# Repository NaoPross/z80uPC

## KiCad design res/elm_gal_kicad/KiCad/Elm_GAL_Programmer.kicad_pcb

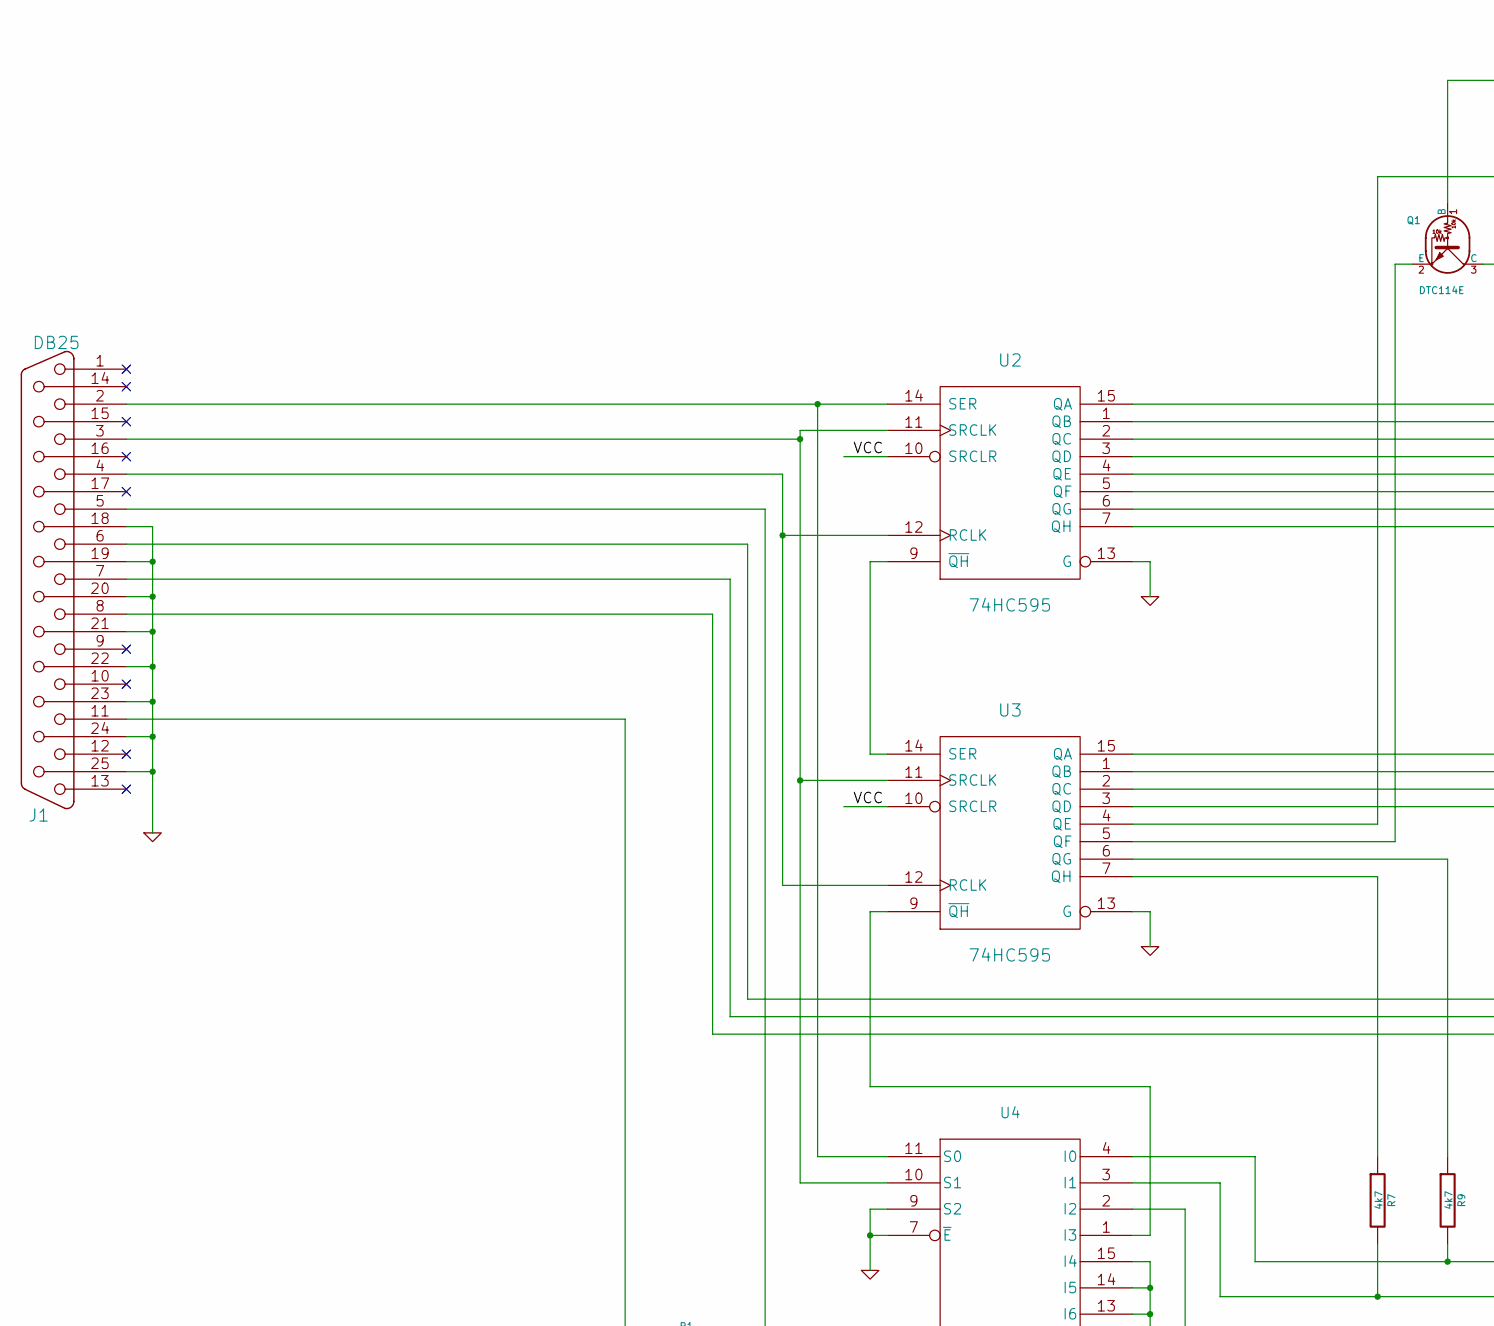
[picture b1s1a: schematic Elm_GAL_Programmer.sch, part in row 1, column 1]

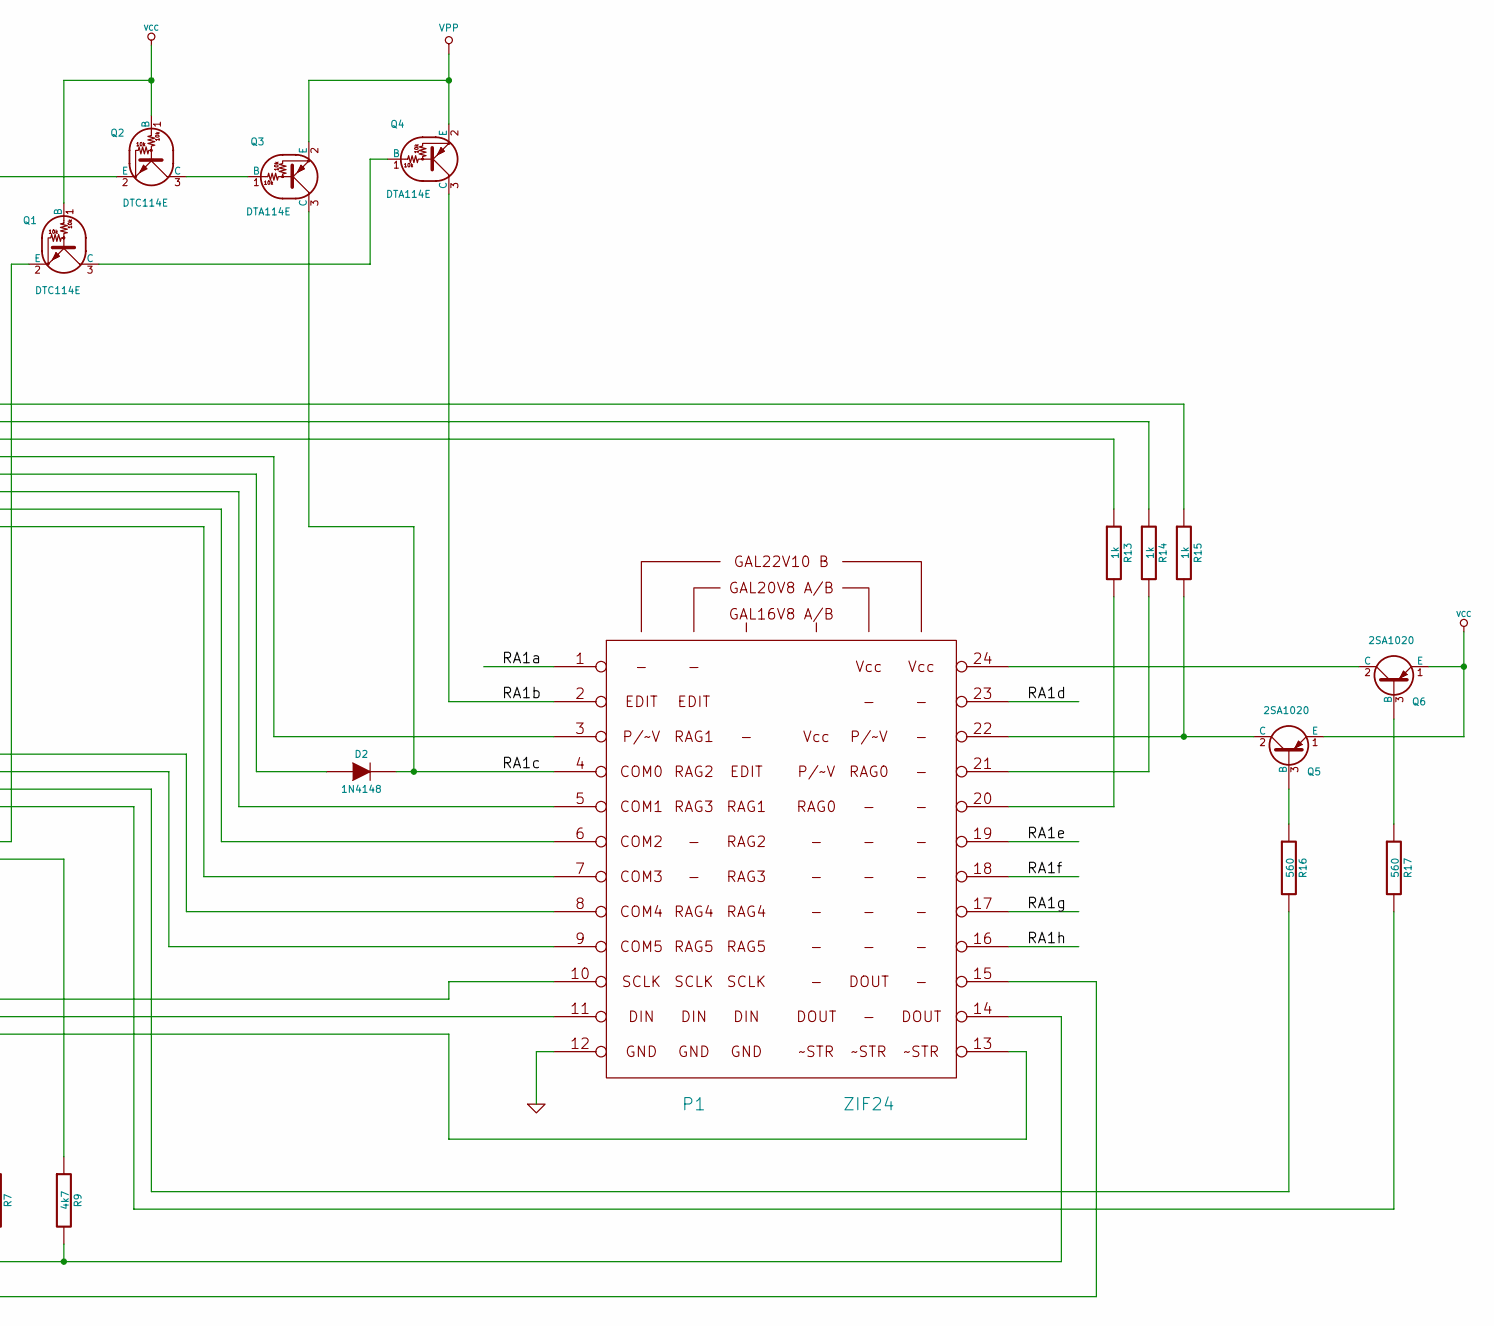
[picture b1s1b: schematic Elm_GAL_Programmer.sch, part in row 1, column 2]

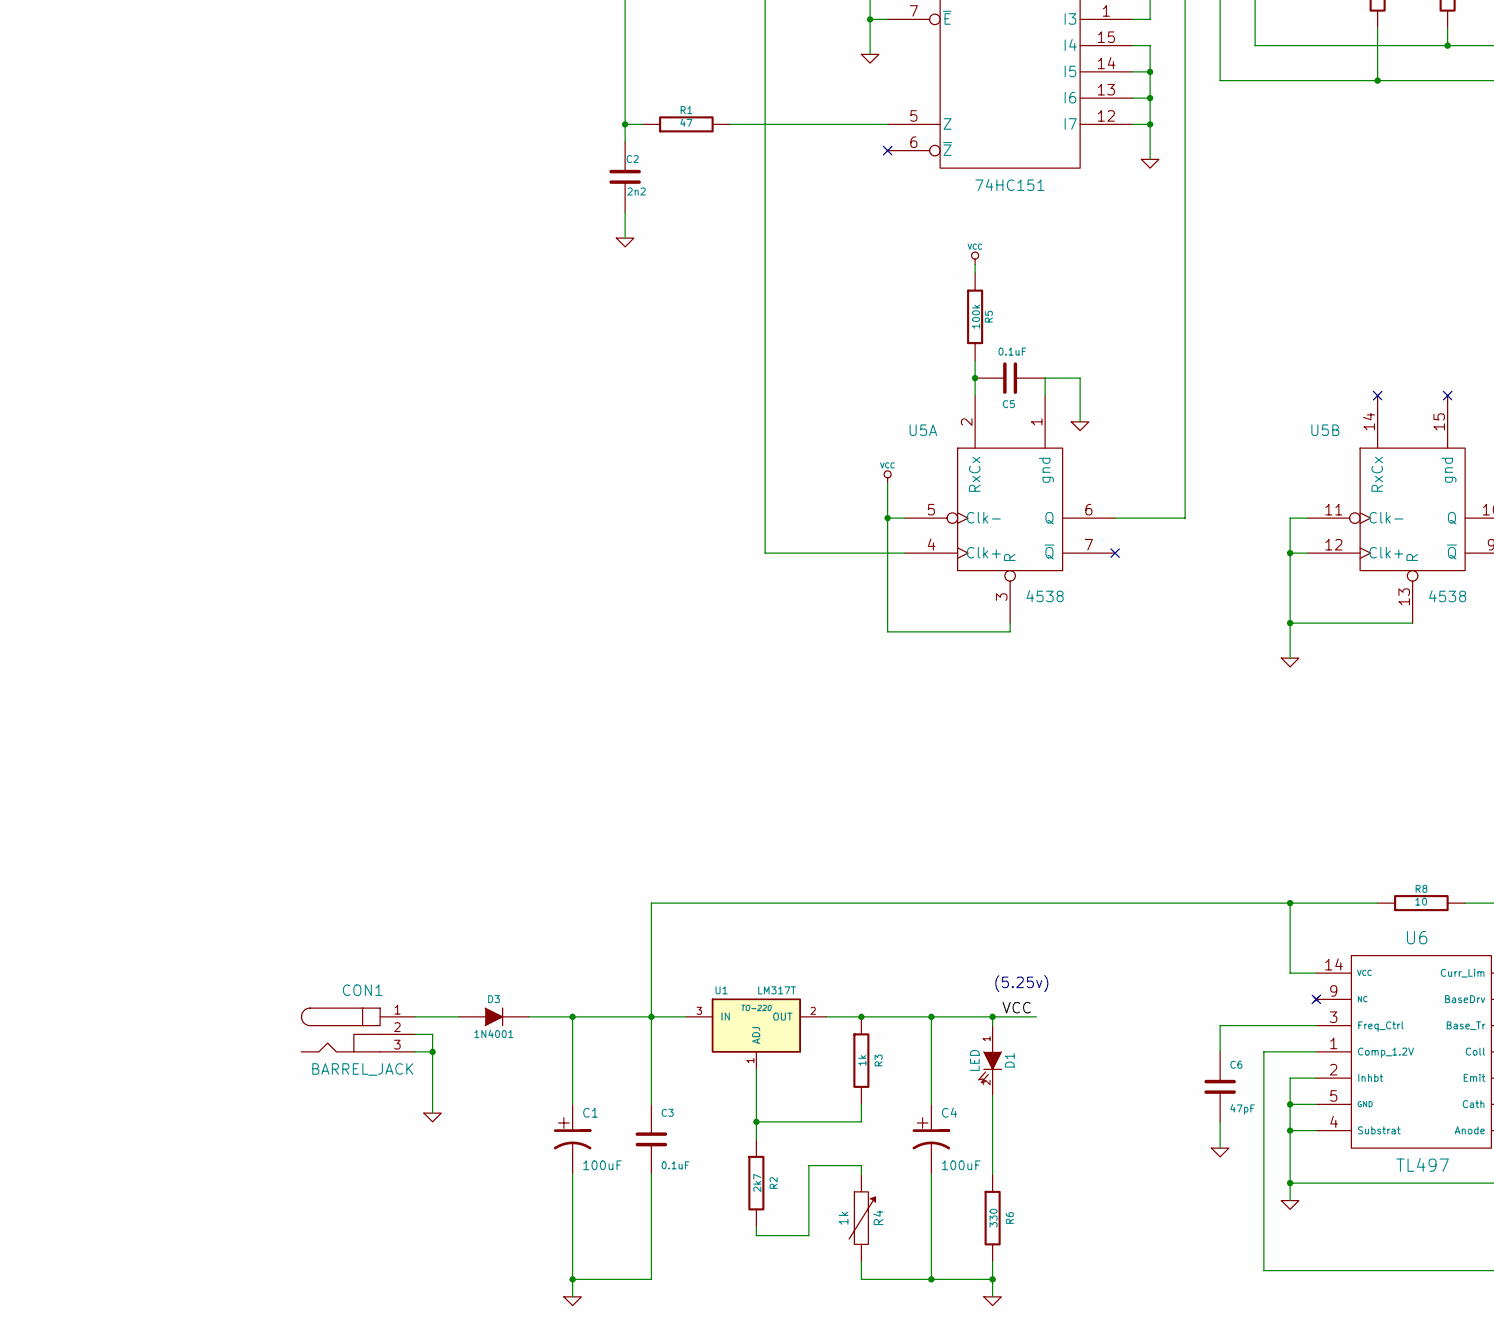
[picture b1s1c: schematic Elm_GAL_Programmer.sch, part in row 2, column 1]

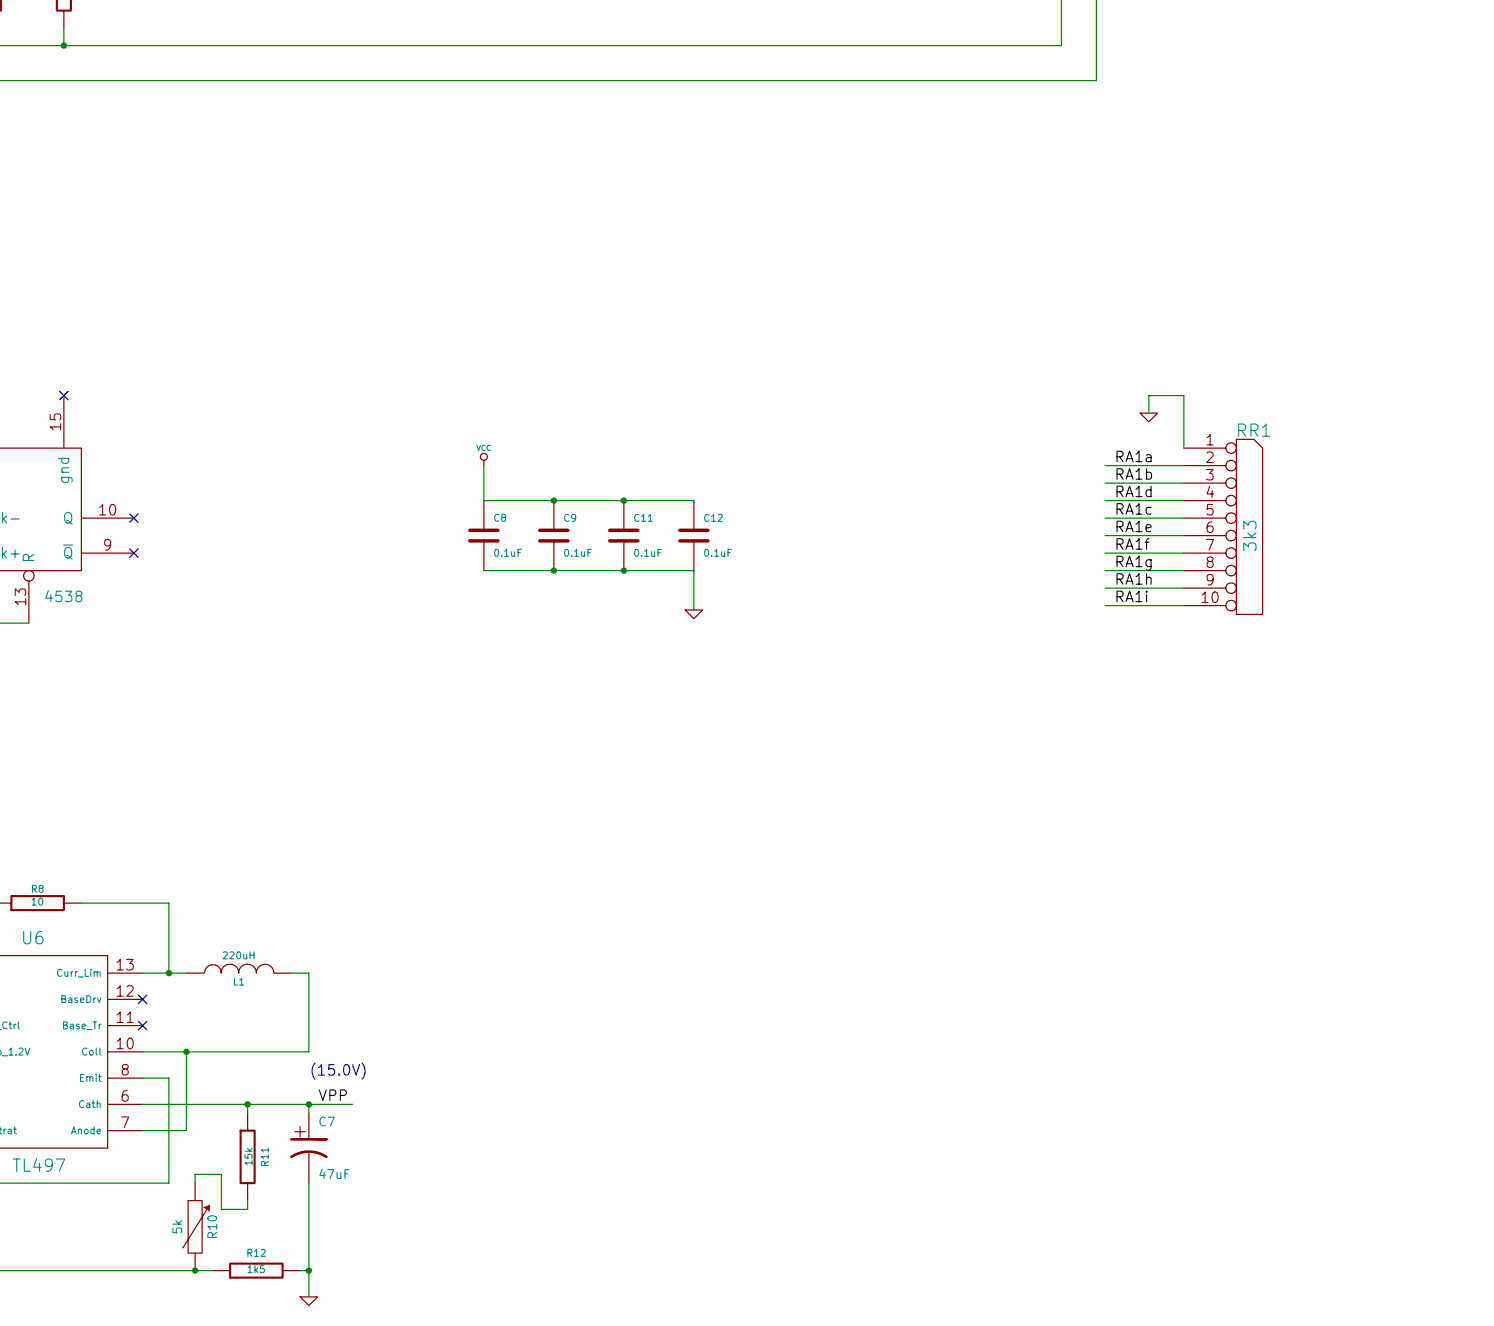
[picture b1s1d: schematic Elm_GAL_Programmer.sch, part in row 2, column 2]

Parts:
C1, C4: 100uF
C2: 2n2
C3, C5, C8, C9, C11, C12: 0.1uF
C6: 47pF
C7: 47uF
CON1: BARREL_JACK
D1: LED
D2: 1N4148
D3: 1N4001
J1: DB25
L1: 220uH
P1: ZIF24
Q1, Q2: DTC114E
Q3, Q4: DTA114E
Q5, Q6: 2SA1020; TO92
R1: 47
R2: 2k7
R3, R4, R13, R14, R15: 1k
R5: 100k
R6: 330
R7, R9: 4k7
R8: 10
R10: 5k
R11: 15k
R12: 1k5
R16, R17: 560
RR1: 3k3
U1: LM317T; TO-220
U2, U3: 74HC595
U4: 74HC151
U5: 4538
U6: TL497

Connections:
/RA1a: P1.1, RR1.2
/RA1b: P1.2, Q4.3 (C), RR1.3
/RA1c: D2.2 (K), P1.4, Q3.3 (C), RR1.5
/RA1d: P1.23, RR1.4
/RA1e: P1.19, RR1.6
/RA1f: P1.18, RR1.7
/RA1g: P1.17, RR1.8
/RA1h: P1.16, RR1.9
GND: C1.2, C2.2, C3.2, C4.2, C5.1, C6.2, C7.2, C8.2, C9.2, C11.2, C12.2, CON1.2, CON1.3, J1.18, J1.19, J1.20, J1.21, J1.22, J1.23, J1.24, J1.25, P1.12, R4.2, R6.2, R12.2, RR1.1 (COM), U2.8 (GND), U2.13 (G), U3.8 (GND), U3.13 (G), U4.7 (~E), U4.8 (GND), U4.9 (S2), U4.12 (I7), U4.13 (I6), U4.14 (I5), U4.15 (I4), U5.1 (gnd), U5.8 (GND), U5.11 (Clk-), U5.12 (Clk+), U5.13 (R), U6.2 (Inhbt), U6.4 (Substrat), U6.5 (GND), U6.8 (Emit)
unnamed: P1.21, R14.2
unnamed: P1.9, U3.1 (QB)
unnamed: P1.20, R13.2
unnamed: P1.22, Q5.2 (C), R15.2
unnamed: R13.1, U2.2 (QC)
unnamed: R14.1, U2.1 (QB)
unnamed: R15.1, U2.15 (QA)
unnamed: P1.6, U2.6 (QG)
unnamed: D2.1 (A), U2.4 (QE)
unnamed: P1.5, U2.5 (QF)
unnamed: Q1.3 (C), Q4.1 (B)
unnamed: P1.7, U2.7 (QH)
unnamed: P1.8, U3.15 (QA)
unnamed: J1.5, U5.4 (Clk+)
unnamed: J1.6, P1.10
unnamed: J1.7, P1.11
unnamed: J1.8, P1.13
unnamed: P1.15, R7.2, U4.3 (I1)
unnamed: R9.1, U3.6 (QG)
unnamed: P1.14, R9.2, U4.4 (I0)
unnamed: U4.2 (I2), U5.6 (Q)
unnamed: P1.3, U2.3 (QD)
unnamed: Q2.2 (E), U3.4 (QE)
unnamed: Q1.2 (E), U3.5 (QF)
unnamed: R7.1, U3.7 (QH)
unnamed: C2.1, J1.11, R1.1
unnamed: CON1.1, D3.1 (A)
unnamed: R16.2, U3.2 (QC)
unnamed: Q6.3 (B), R17.1
unnamed: R17.2, U3.3 (QD)
unnamed: Q5.3 (B), R16.1
unnamed: P1.24, Q6.2 (C)
unnamed: L1.2, U6.7 (Anode), U6.10 (Coll)
unnamed: R10.2, R12.1, U6.1 (Comp_1.2V)
unnamed: L1.1, R8.2, U6.13 (Curr_Lim)
unnamed: C5.2, R5.2, U5.2 (RxCx)
unnamed: R10.1, R11.2
unnamed: C6.1, U6.3 (Freq_Ctrl)
unnamed: R2.1, R3.2, U1.1 (ADJ)
unnamed: R2.2, R4.1
unnamed: D1.2 (K), R6.1
unnamed: C1.1, C3.1, D3.2 (K), R8.1, U1.3 (IN), U6.14 (VCC)
unnamed: U2.9 (~QH), U3.14 (SER)
unnamed: J1.3, U2.11 (SRCLK), U3.11 (SRCLK), U4.10 (S1)
unnamed: R1.2, U4.5 (Z)
unnamed: J1.4, U2.12 (RCLK), U3.12 (RCLK)
unnamed: U3.9 (~QH), U4.1 (I3)
unnamed: Q2.3 (C), Q3.1 (B)
unnamed: J1.2, U2.14 (SER), U4.11 (S0)
VCC: C4.1, C8.1, C9.1, C11.1, C12.1, D1.1 (A), Q1.1 (B), Q2.1 (B), Q5.1 (E), Q6.1 (E), R3.1, R5.1, U1.2 (OUT), U2.10 (SRCLR), U2.16 (VCC), U3.10 (SRCLR), U3.16 (VCC), U4.16 (VCC), U5.3 (R), U5.5 (Clk-), U5.16 (VCC)
VPP: C7.1, Q3.2 (E), Q4.2 (E), R11.1, U6.6 (Cath)

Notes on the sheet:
(5.25v)
(15.0V)

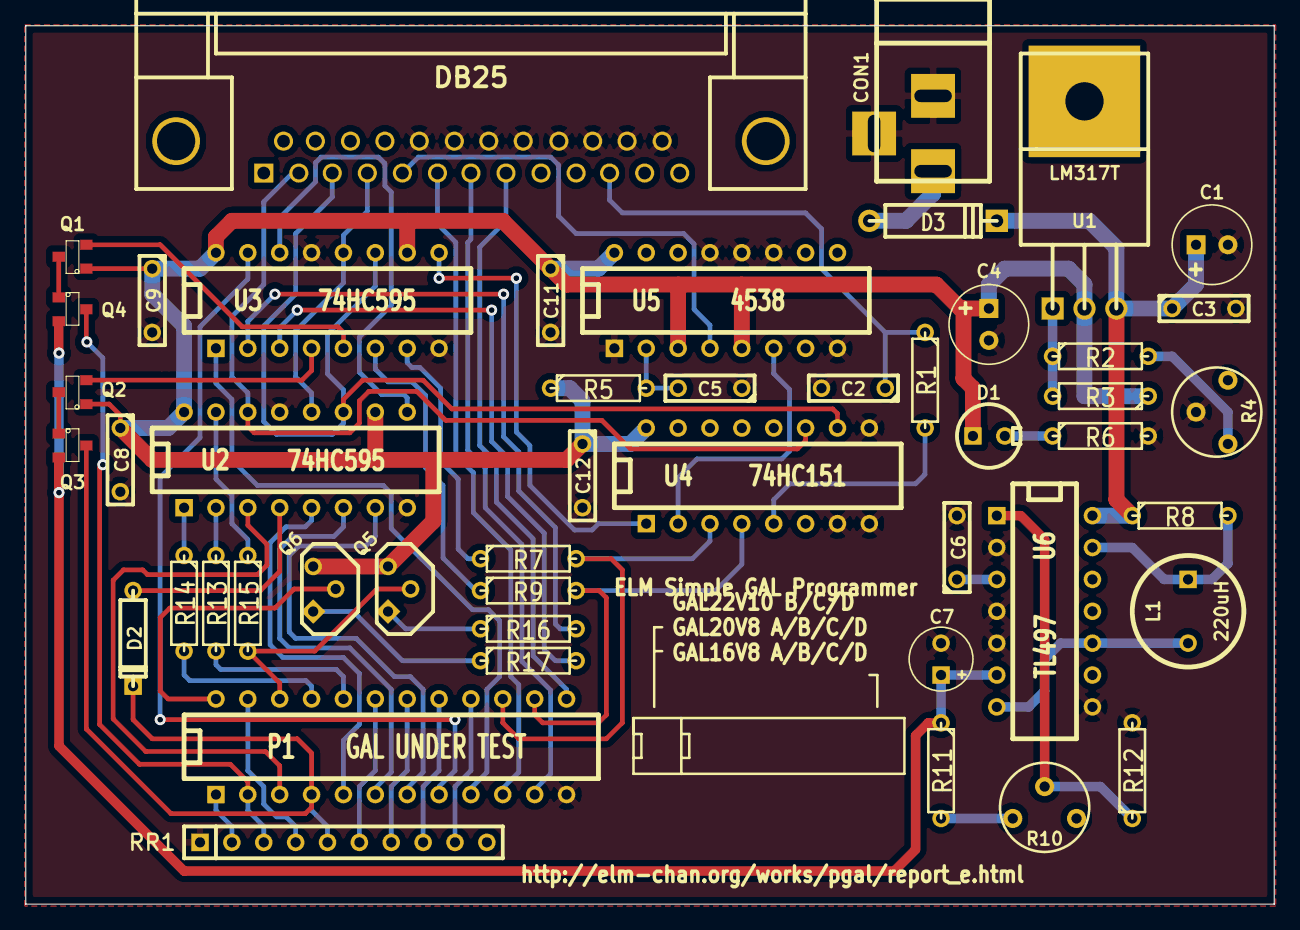
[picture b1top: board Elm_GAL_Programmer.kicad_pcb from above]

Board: 2 copper layers, 99.5 x 70.0 mm, 48 parts (0 on the bottom side), 60 nets.

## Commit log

2017-02-14 first commit, downloaded doc
2017-02-14 hw: created z80acpu in sch library
2017-02-14 sw: copied flash tool source from gameboymod
2017-02-24 hw: created sch, doc: added uart datasheet
2017-02-24 hw: created library project, doc: added 74LS193 datasheet
2017-02-24 doc: added SG51P datasheet
2017-03-05 created doc
2017-03-05 sw: started to implement serial on linux side
2017-03-05 doc: added L7805ACV datasheet; hw: updated scheme
2017-03-06 updated todolist
2017-03-06 hw: moved everything to one sheet
2017-03-07 updated todolist; doc: keyboard stuff
2017-03-17 hardware nearly finished
    doc: added datasheets for
    - GAL16V8
    - MAX214
    - MAX232
    added script to build doc under windows with miktex
    updated notes
2017-03-23 changed scheme layout
    hw: changed scheme and annotated components
    doc: added build script for windows
    sw: added res/ folder with blaster and created jedec document for
    address decoder pld
2017-03-23 created bios/kernel source code structure
2017-03-25 added missing makefile for z80 and fixed gitignore
2017-03-25 Git repository setup
    Git merge from master by atlas
2017-03-31 added iospace address decoder
2017-04-04 schematic complete
    hw: change address decoder chip from GAL16V8 to M4-32/32 (CPLD)
    change main bus connector with a custom one (intead of PC/104)
    start building footprint library
2017-04-13 switch from GAL (pld) to M4 32/32 CPLD
    add M4 32/32 CPLD datasheet
    new VHDL code with better control over the address space thanks to the
    M4 which has a 16 bit input port
2017-04-13 scheme update and PCB start
    add missing capacitor and resistor values (serial XTAL)
    create new eurocard standard compliant PCB for the uPC
    and other minor fixes
2017-04-28 start printed circuit board design
    wired:
    - clock circiuts
    - reset button
    set layout for:
    - CPU & memory
    - serial interface
2017-05-01 switch to sdcc
    - update of the makefile to use sdcc, since it is more popular and
    it's easier to insall on other computers
    - fix of crt0.s (old loader.asm) for the new compiler
    - change of the structure in the source code folder to separate
    betweeen libc and kernel code
2017-05-02 fix for sdcc makefile
    fix for the old makefile, because it could't compile more than one source file.
    new libc directory with mem.c to start implementing the standard C library
    (or at least the part we need).
2017-05-02 Basic sys io setup
2017-05-02 sysio.h libc interface
2017-05-02 add serial device struct
    other changes:
    - change from main() to kmain() in crt0.s and kernel.c
    - new file devices.h to define all address locations for devices
    - new data type
    - register_t as volatile uint8_t for registers in devices
    - size_t from libc
2017-05-03 new file coding_rules.txt to have a consistent coding style
2017-05-04 Kernel memory mapping setup
2017-05-05 add switches datasheets for footprints
2017-05-05 complete wiring for serial interface connector and logic
    other changes:
    - new layout, probably the board will have to be resized to a
    nonstandard size (currently 2EUROCARD)
    - new footprint HDR5x2_SOCKET for standard 5x2 flatcable connectors
2017-05-09 created new layout (starting over)
    the old layout is still under hw/MainBoard1.PcbDoc
2017-05-18 wires from DB-9 and HDR5x2 connector to MAX214 (U7) and crystal for TL16C550
2017-05-18 wiring for P4 and P5 (I/O ports) and circuits for CLKs and RST
2017-05-18 wiring for CTC (U8) to address bus and data bus
2017-05-18 new traces for cpu signals and for high address to the MMU / addr decoder
    there are also many other minor changes to connect various wires
2017-05-19 wiring for 7 segment displays and traces for the remaining CPU signals
2017-05-19 finish wiring and add eurocard compliant standard holes
    since there wasn't enough space (I should have added the holes before
    beginning) there are only 4 holes instead of 6 (2 will be cut out
    since the space is unused).
2017-05-23 board complete, generate gerber (x2) files
    this is probably the last commit before printing the PCB, unless there are some
    other errors in the board design
2017-06-02 add serial interface and a few std library functions
    changes in usart:
    - new functions to setup the serial comunication settings such as baudrate,
    parity and stop bits
    - init function with most common values
    - transmit and receive functions each with a wrapper to send data blocks
    changes in libc:
2017-06-10 add port interface header, api still to implement
    fix for bug in usart.c, in function usart_write() that checked the
    trasmission_empty register at the wrong time causing it to overwrite
    the buffer.
2017-06-15 new documentation in z80upc.pdf
2017-06-15 Boot loader structures (WORK IN PROGRESS) Some Program manager structures, macros and functions (WORK IN PROGRESS)
2017-06-16 fixed typo in usart.h and in doc
2017-06-16 new components list and cpld test unit
2017-06-19 Authentication section Programs management
2017-06-19 libc memset, memcmp boot improved program allocation
2017-06-23 Order and update of the struct Separation of boot and login sections Improuved program manager system
2017-07-04 new structure for process management, structures to discuss
    the idea behind kernel/include/progman.h was good but the implementation was
    very not unix-like, so I made a new file under
    kernel/include/process.h that will implement the same features
    other changes:
    - move usart register structs definitions outside of the device
    - remove old build files
2017-07-31 filesystem structure intro and docs
    - new type pid_t and program management mechanism to make it
    easier to switch to a multitasking kernel
    - new memory related functions in memory.h to move, copy and
    manage pages
    - fix typos
2017-08-07 implementation for avr programmer
    the programmer will receive the binary in blocks of defined size
    by a program under sw/programmer/linux (moved from sw/linux).
2017-08-08 updated .gitignore
2017-08-23 new programmer interface for linux
    there is a new program with GUI (gtk3) to send data to its avr
    conterpart.
    it needs to be tested, since there may be a few bugs in it;
    building a GUI was a terrible idea.
2017-08-23 Filesystem struct order
2017-08-25 implements pio.h functions and makefile update to optimize size
    - remove syscall.h, unused and not implemented
    - bug fix for memcmp() in string.c
    other changes are still partially unfinished and might not work
2017-08-26 File system initialization
    Simple I/O (sio) interfaced, not yet implemented
2017-08-26 edit documentation abstract
2017-08-26 time to inode
2017-08-26 update gitignore to ignore sdcc output
2017-08-28 add test program for z80
2017-08-31 File system interface Basic file system implementation Path resolution work in progress
2017-08-31 Some untracked files from last commit
2017-08-31 macro fix
2017-09-07 minor bug fix for ROM programmer
2017-09-07 z80_test cleanup and makefile corrections
2017-09-10 new documentation with no styling
    the old documentation was written more like a journal than a proper
    paper, so I am rewriting in a separate document. Once the new doc
    will be completed, the content of the old one will be discarted.
2017-09-10 partial implementation for ctc drivers and memory management
2017-10-05 Test units are now in their own folder 'z80_test', add programmer cli interface
2017-10-05 Move test units to z80/tests, and drivers are now statically linked
    Makefiles for the test units were getting messier, so now drivers
    (that need to be tested) are statically compiled in their own
    folder under z80/drivers.
    The kernel makefile and is now broken since everything has been moved.
2017-10-19 Fix for PIO driver and its test and deletes build files
2017-10-19 Got a real rom programmer, this code is still broken but I don't care
2017-10-19 Update gitignore and add sdcc manual
2017-11-05 Continues both hw and sw doc
2017-11-09 Update makefile, and bug fix in pio driver and usart
2017-11-14 Update doc, remove z80uPC.tex, improved z80uPC_nostyle
    it was useless to have 2 copies of the same thing,
    soon z80uPC_nostyle will be renamed to z80uPC
2017-11-14 Improvements in PIO driver, pio test rewritten in inline asm
2017-11-23 update cpld files from VHDL dev machine and delete programmer code (unused)
2017-11-23 remove unused TODO file
2017-11-28 Add datasheets and resources
2018-10-30 Remove uselss resources
2018-10-30 Add datasheets for ATmega328 and 74LS259
2018-10-30 Move sw to sw-old and hw to hw-altium, add kicad files
2018-10-30 Create avr project for ROM loader
2018-10-30 Update gitignore
2018-10-30 [avr] Add test program for IO and basic usart
2018-10-31 [linux] Add initial implementation of rom-loader
2018-10-31 [avr] Implement set_addr(addr) to control 74LS259 chips
2018-10-31 Add Z80 user manual
2018-11-01 [z80] Add hello project
2018-12-01 [linux] Add debug build flag to rom-loader
